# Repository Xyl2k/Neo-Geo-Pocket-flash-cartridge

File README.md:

# Neo-Geo-Pocket-flash-cartridge
Board layout based on furrtek schematic: http://furrtek.free.fr/?p=crea&a=cartflash as he haven't since time released a typon.
There is one issue thought: the connector size, i don't know it, so i have no idea if my board layout will fit in a real neo geo pocket.

/!\ Don't produce for the moment /!\

or if you have a caliper and a NGP cartridge, feel free to correct the board size and rearrange connectors
You need also a cpld or another Uc to pass the verification check.

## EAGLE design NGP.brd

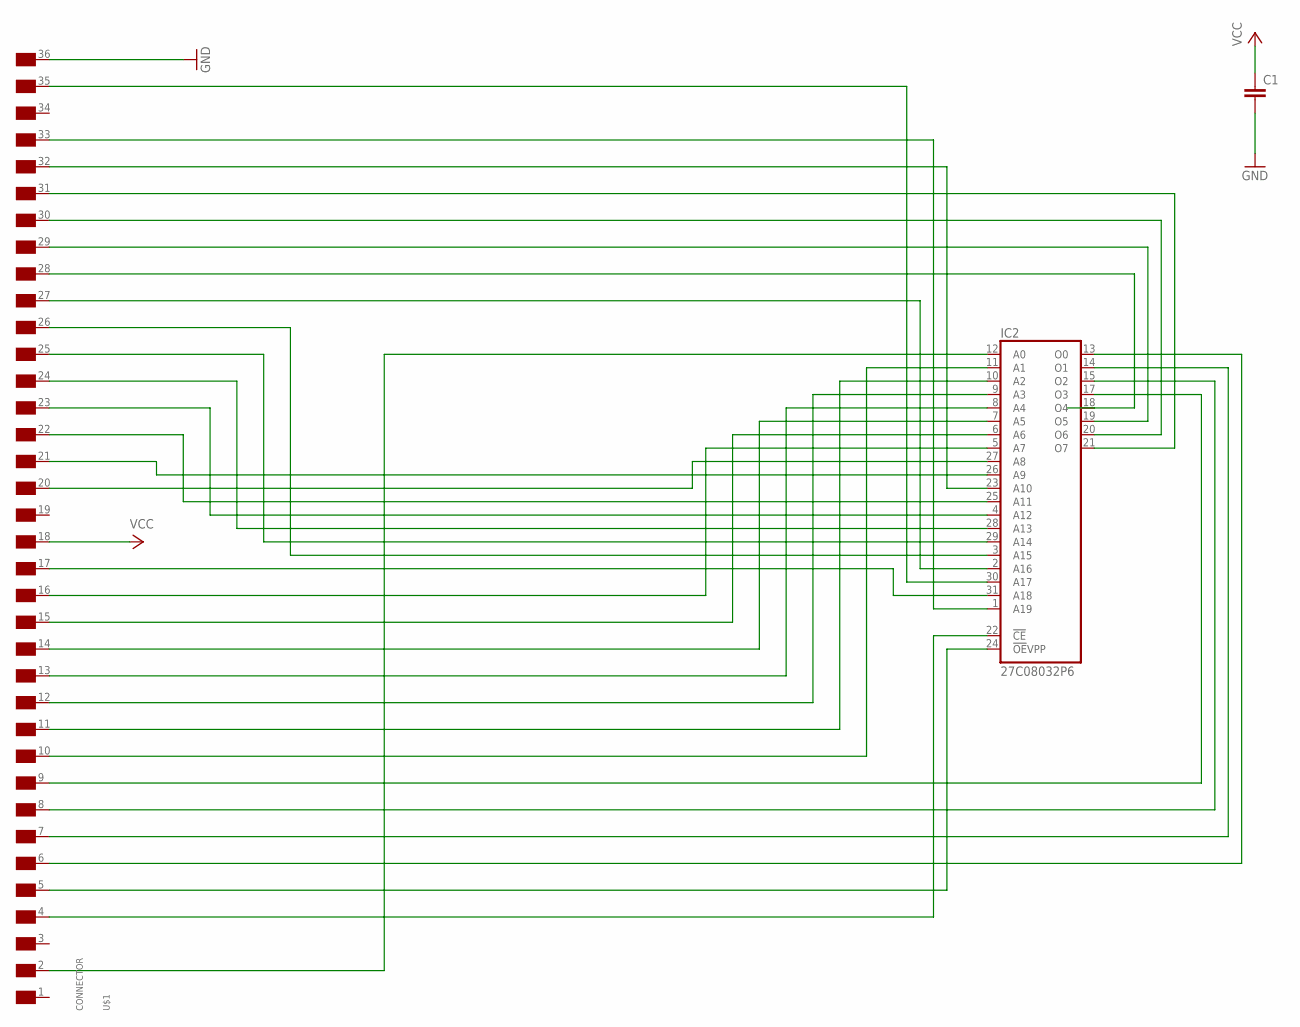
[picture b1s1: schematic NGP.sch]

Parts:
C1: C-EU025-024X044; C025-024X044
IC2: 27C08032P6; DIL32
U$1: CONNECTOR

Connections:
GND: C1.2, IC2.16 (GND), U$1.36 (GND1)
unnamed: IC2.18 (O4), U$1.28 (D6)
unnamed: IC2.29 (A14), U$1.25 (D3)
unnamed: IC2.12 (A0), U$1.2 (NC)
unnamed: IC2.22 (!CE), U$1.4 (/RD)
unnamed: IC2.24 (!OE!VPP), U$1.5 (/RCS)
unnamed: IC2.13 (O0), U$1.6 (A0)
unnamed: IC2.14 (O1), U$1.7 (A1)
unnamed: IC2.15 (O2), U$1.8 (A2)
unnamed: IC2.17 (O3), U$1.9 (A3)
unnamed: IC2.11 (A1), U$1.10 (A4)
unnamed: IC2.10 (A2), U$1.11 (A5)
unnamed: IC2.9 (A3), U$1.12 (A6)
unnamed: IC2.8 (A4), U$1.13 (A7)
unnamed: IC2.7 (A5), U$1.14 (A8)
unnamed: IC2.6 (A6), U$1.15 (A9)
unnamed: IC2.5 (A7), U$1.16 (A10)
unnamed: IC2.31 (A18), U$1.17 (A11)
unnamed: IC2.27 (A8), U$1.20 (A14)
unnamed: IC2.26 (A9), U$1.21 (A15)
unnamed: IC2.25 (A11), U$1.22 (D0)
unnamed: IC2.4 (A12), U$1.23 (D1)
unnamed: IC2.28 (A13), U$1.24 (D2)
unnamed: IC2.3 (A15), U$1.26 (D4)
unnamed: IC2.2 (A16), U$1.27 (D5)
unnamed: IC2.30 (A17), U$1.35 (VIN1)
unnamed: IC2.1 (A19), U$1.33 (D8)
unnamed: IC2.19 (O5), U$1.29 (D7)
unnamed: IC2.20 (O6), U$1.30 (/RS)
unnamed: IC2.21 (O7), U$1.31 (VIN)
unnamed: IC2.23 (A10), U$1.32 (GND)
VCC: C1.1, IC2.32 (VCC), U$1.18 (A12)
VDD: U$1.1 (VDD)

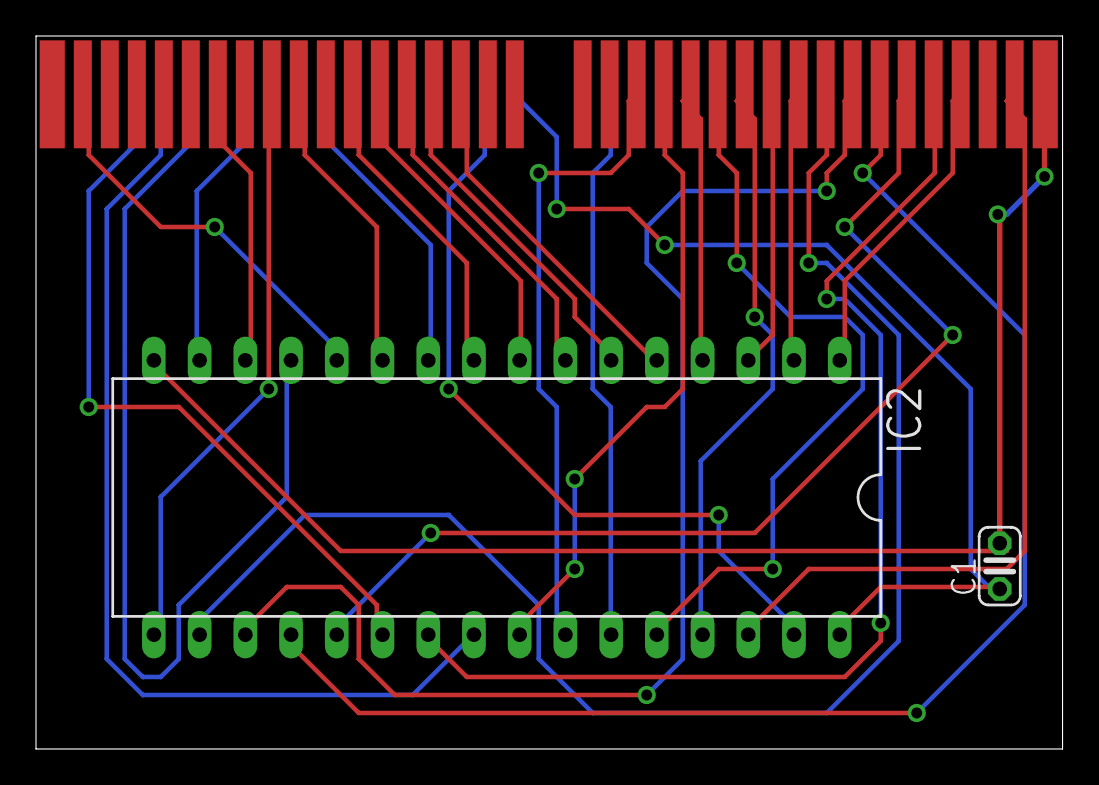
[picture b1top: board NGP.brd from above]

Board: 2 copper layers, 57.0 x 39.6 mm, 3 parts (0 on the bottom side), 32 nets.

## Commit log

2015-01-15 :octocat: Added .gitattributes & .gitignore files
2015-01-15 1.0
    1.0
